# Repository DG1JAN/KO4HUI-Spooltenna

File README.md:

# KO4HUI-Spooltenna
This repository contains design files for the Spooltenna(TM) end fed half wave antenna used for portable amateur radio operating.

The design files in this repository were created with KiCad 8.0 and information on how to use this tool can be found here: https://docs.kicad.org/8.0/.

## License

This project is licensed under the Creative Commons Attribution-ShareAlike 4.0 International License. To view a copy of this license, visit [https://creativecommons.org/licenses/by-sa/4.0/](https://creativecommons.org/licenses/by-sa/4.0/).

### Attribution

- Creator: Rob Bowser

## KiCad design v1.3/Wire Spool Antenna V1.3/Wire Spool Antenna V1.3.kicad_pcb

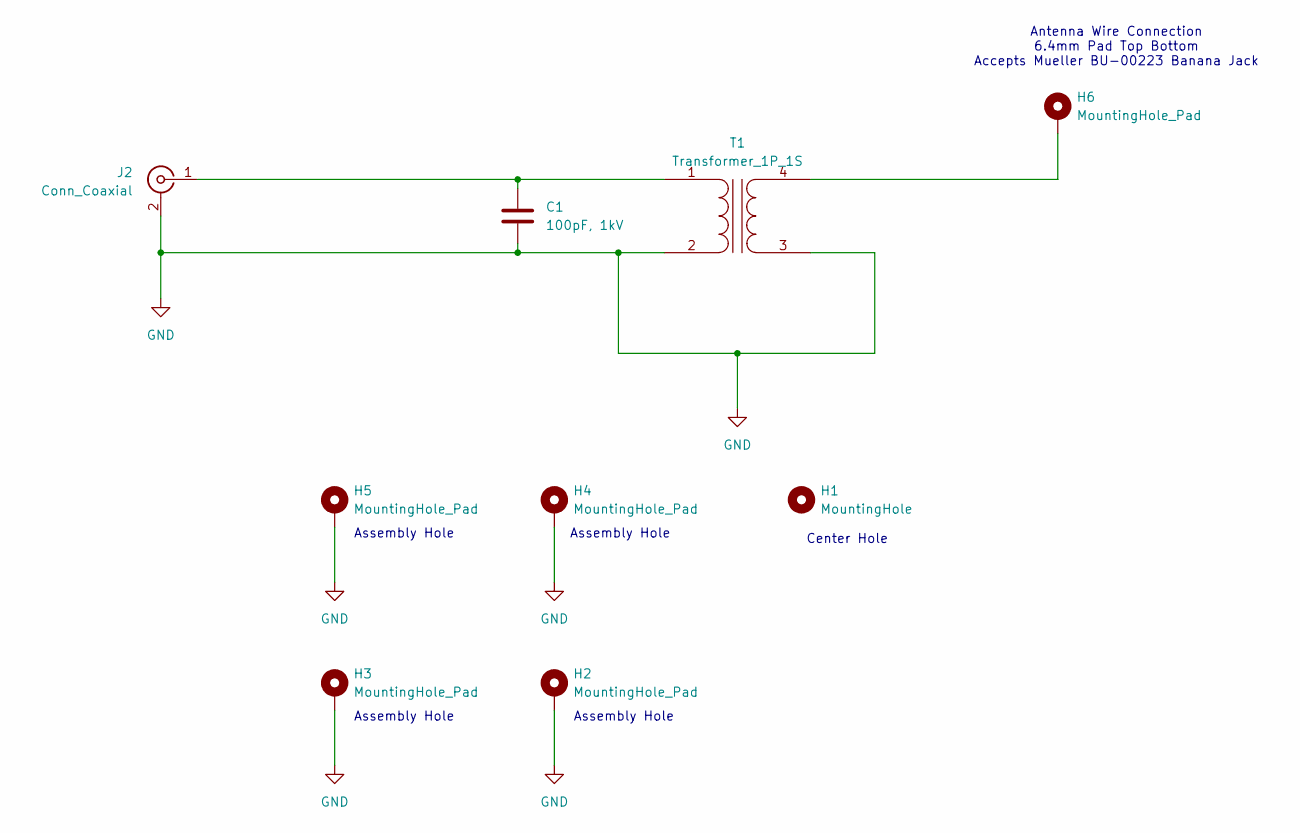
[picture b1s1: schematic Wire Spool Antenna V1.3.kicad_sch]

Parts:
C1: 100pF, 1kV; C_Disc_D7.5mm_W4.4mm_P5.00mm_OPT
H1: MountingHole; MountingHole_8.4mm_M8
H2, H3, H4, H5: MountingHole_Pad; MountingHole_3.2mm_M3_Pad_TopBottom
H6: MountingHole_Pad; MountingHole_6.4mm_M6_Pad_TopBottom
J2: Conn_Coaxial; BNC_MOLEX_73100_PIPE
T1: Transformer_1P_1S; TOROID_140_AUTO_OPT

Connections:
GND: C1.2, H2.1, H3.1, H4.1, H5.1, J2.2 (Ext), T1.2 (AB), T1.3 (SA)
unnamed: C1.1, J2.1 (In), T1.1 (AA)
unnamed: H6.1, T1.4 (SB)

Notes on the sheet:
Assembly Hole
Antenna Wire Connection 6.4mm Pad Top Bottom Accepts Mueller BU-00223 Banana Jack
Center Hole

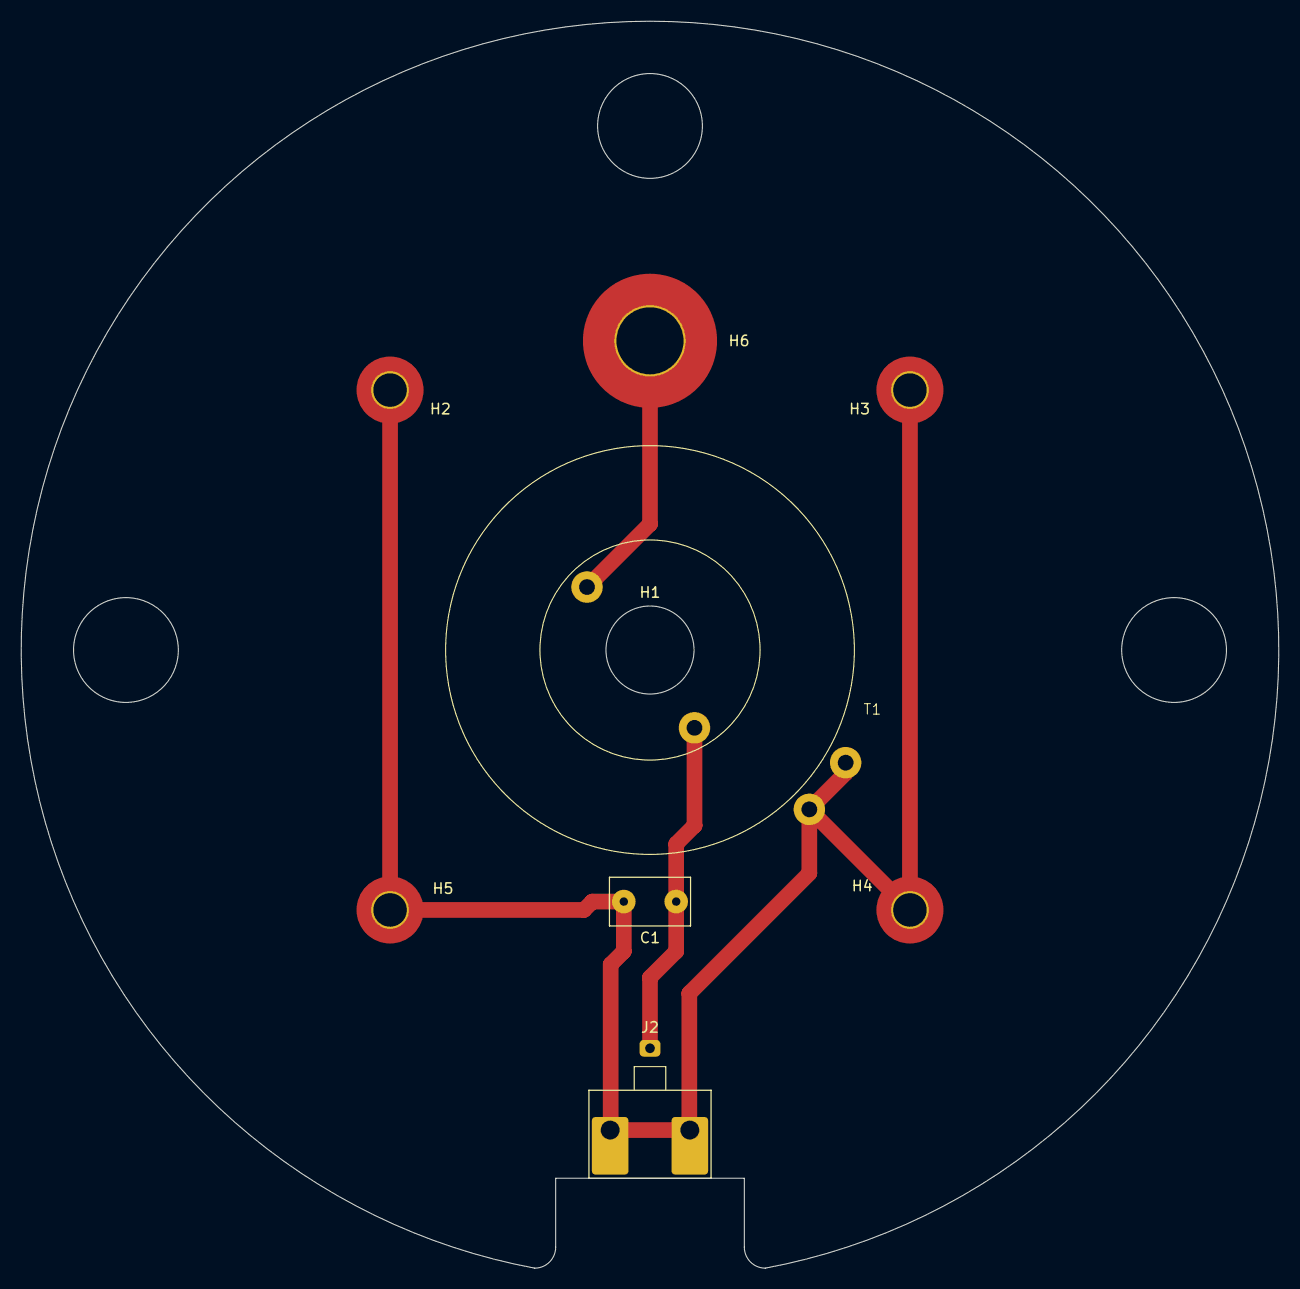
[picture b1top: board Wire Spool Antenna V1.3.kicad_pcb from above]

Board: 2 copper layers, 120.0 x 119.0 mm, 9 parts (0 on the bottom side), 3 nets.

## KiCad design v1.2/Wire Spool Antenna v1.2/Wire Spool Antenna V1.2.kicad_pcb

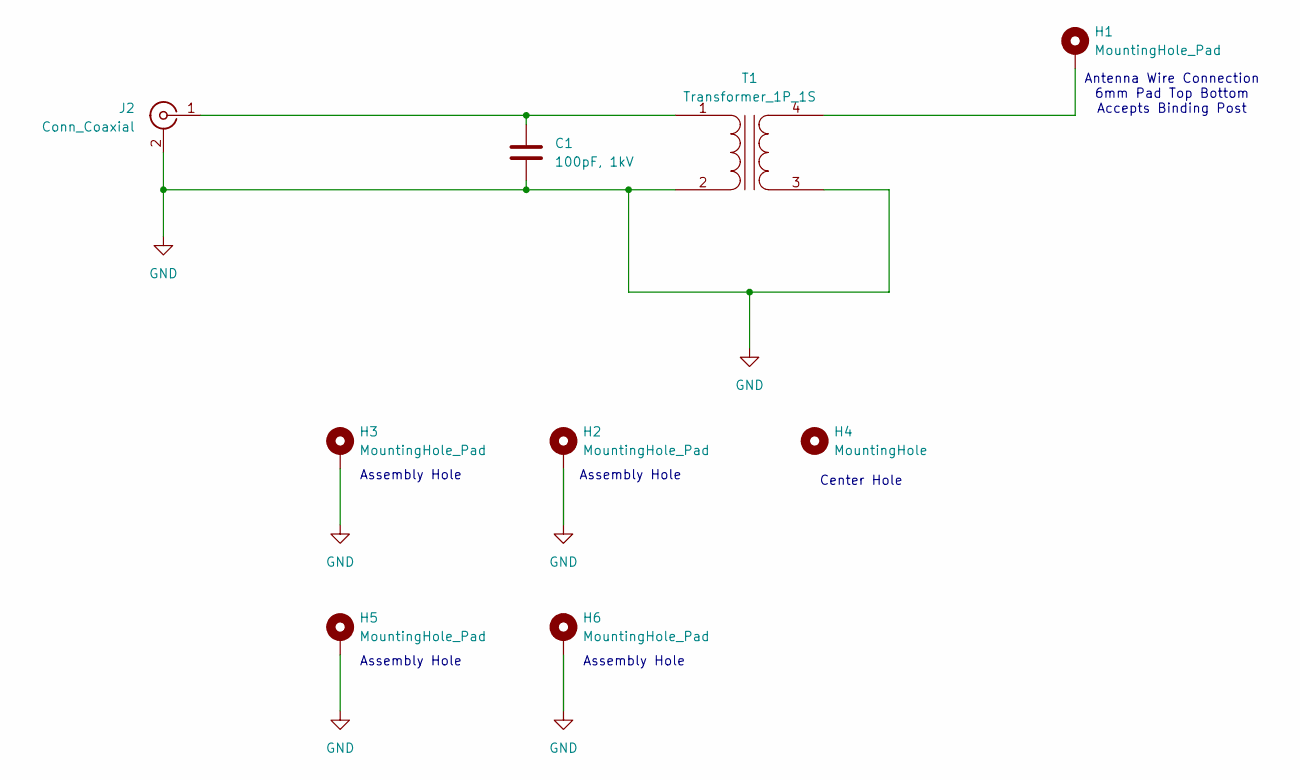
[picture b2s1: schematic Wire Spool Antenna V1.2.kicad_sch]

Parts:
C1: 100pF, 1kV; C_Disc_D7.5mm_W4.4mm_P5.00mm
H1: MountingHole_Pad; MountingHole_6mm_Pad_TopBottom
H2, H3, H5, H6: MountingHole_Pad; MountingHole_3.2mm_M3_Pad
H4: MountingHole; MountingHole_8.4mm_M8
J2: Conn_Coaxial; BNC_MOLEX_73100
T1: Transformer_1P_1S; TOROID_140_AUTO

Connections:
GND: C1.2, H2.1, H3.1, H5.1, H6.1, J2.2 (Ext), T1.2 (AB), T1.3 (SA)
unnamed: C1.1, J2.1 (In), T1.1 (AA)
unnamed: H1.1, T1.4 (SB)

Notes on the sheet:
Assembly Hole
Antenna Wire Connection 6mm Pad Top Bottom Accepts Binding Post
Center Hole

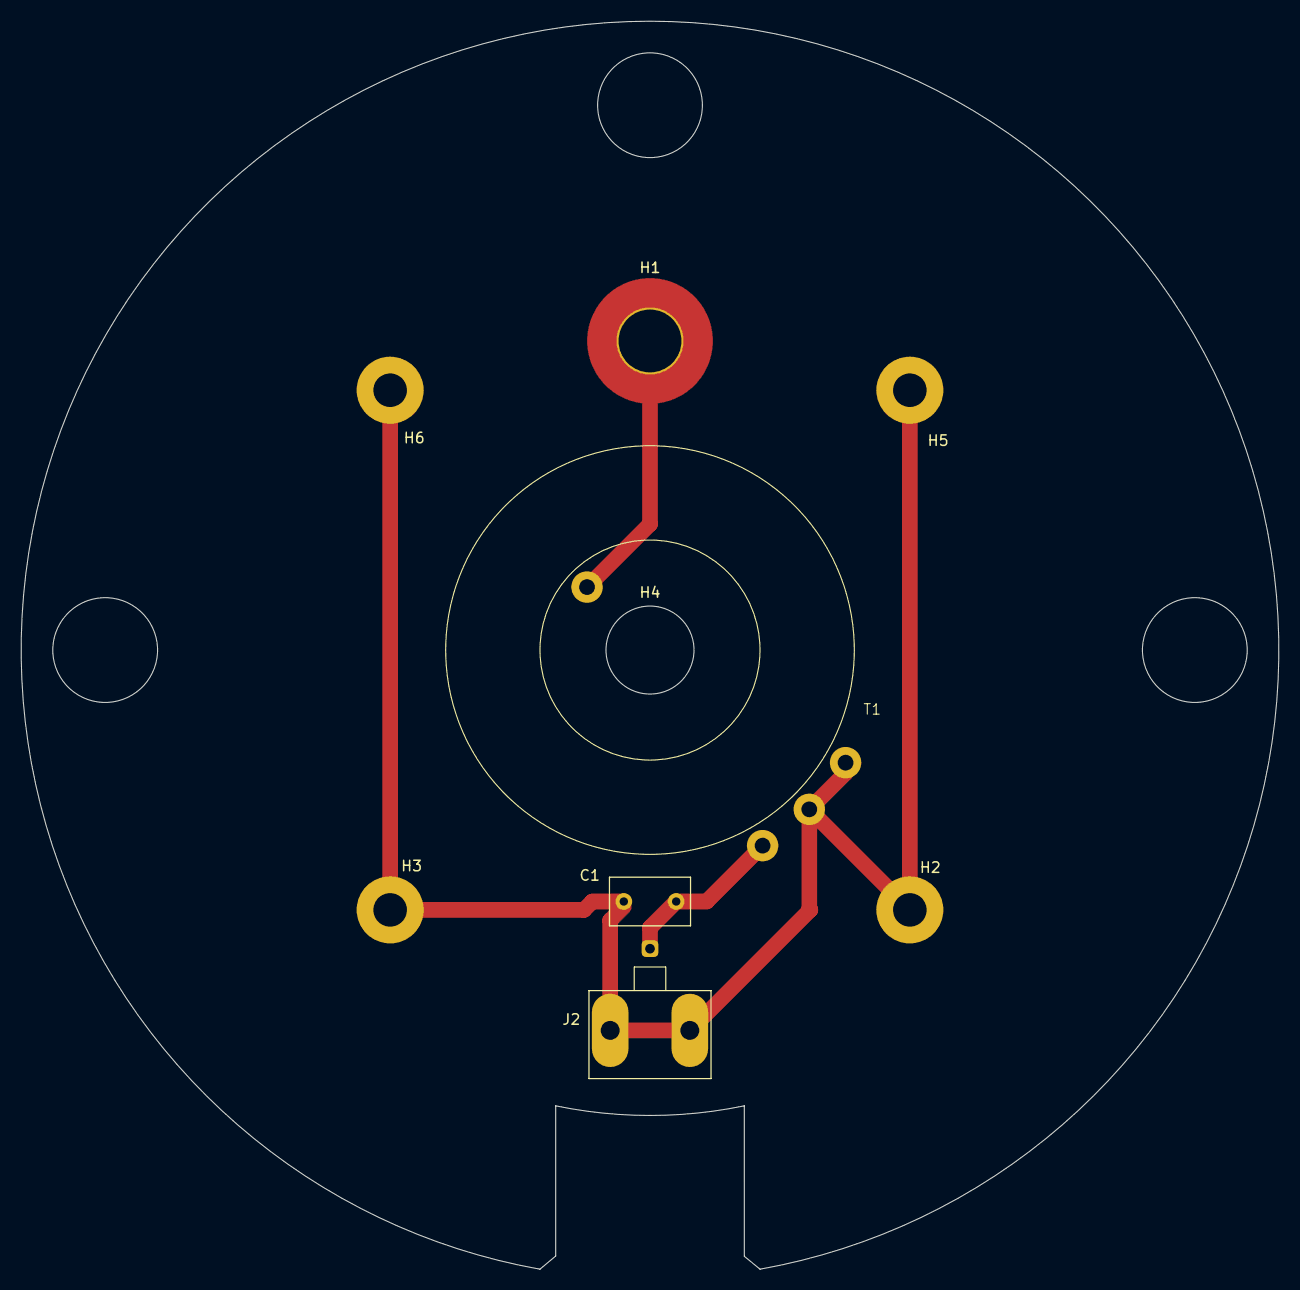
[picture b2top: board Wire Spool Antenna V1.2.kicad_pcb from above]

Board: 2 copper layers, 120.0 x 119.1 mm, 9 parts (0 on the bottom side), 3 nets.
